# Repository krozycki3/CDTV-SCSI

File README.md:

# CDTV-SCSI

SCSI expansion board for Amiga CDTV

    - Implementation of the Commodore reference design (A575)
    - internal 50 pin SCSI connector
    - internal 68 pin SCSI connector (in 8bit mode)
    - passive termination (2x220,2x330 or 2 x 220/330 THT)
    - switchable clock 16Mhz / 7MHz for WD33C93A / AM33C93A
    - disable jumper
    - activity LED
    - supports autoconfig and autoboot (scsi.device)
    - maximum partition size with ROM v2.30: 1GB
    
The inspiration was the SCSI CDTV controller performed by Matthias Heinrichs (http://amiga.resource.cx/exp/mhcdtvscsi).

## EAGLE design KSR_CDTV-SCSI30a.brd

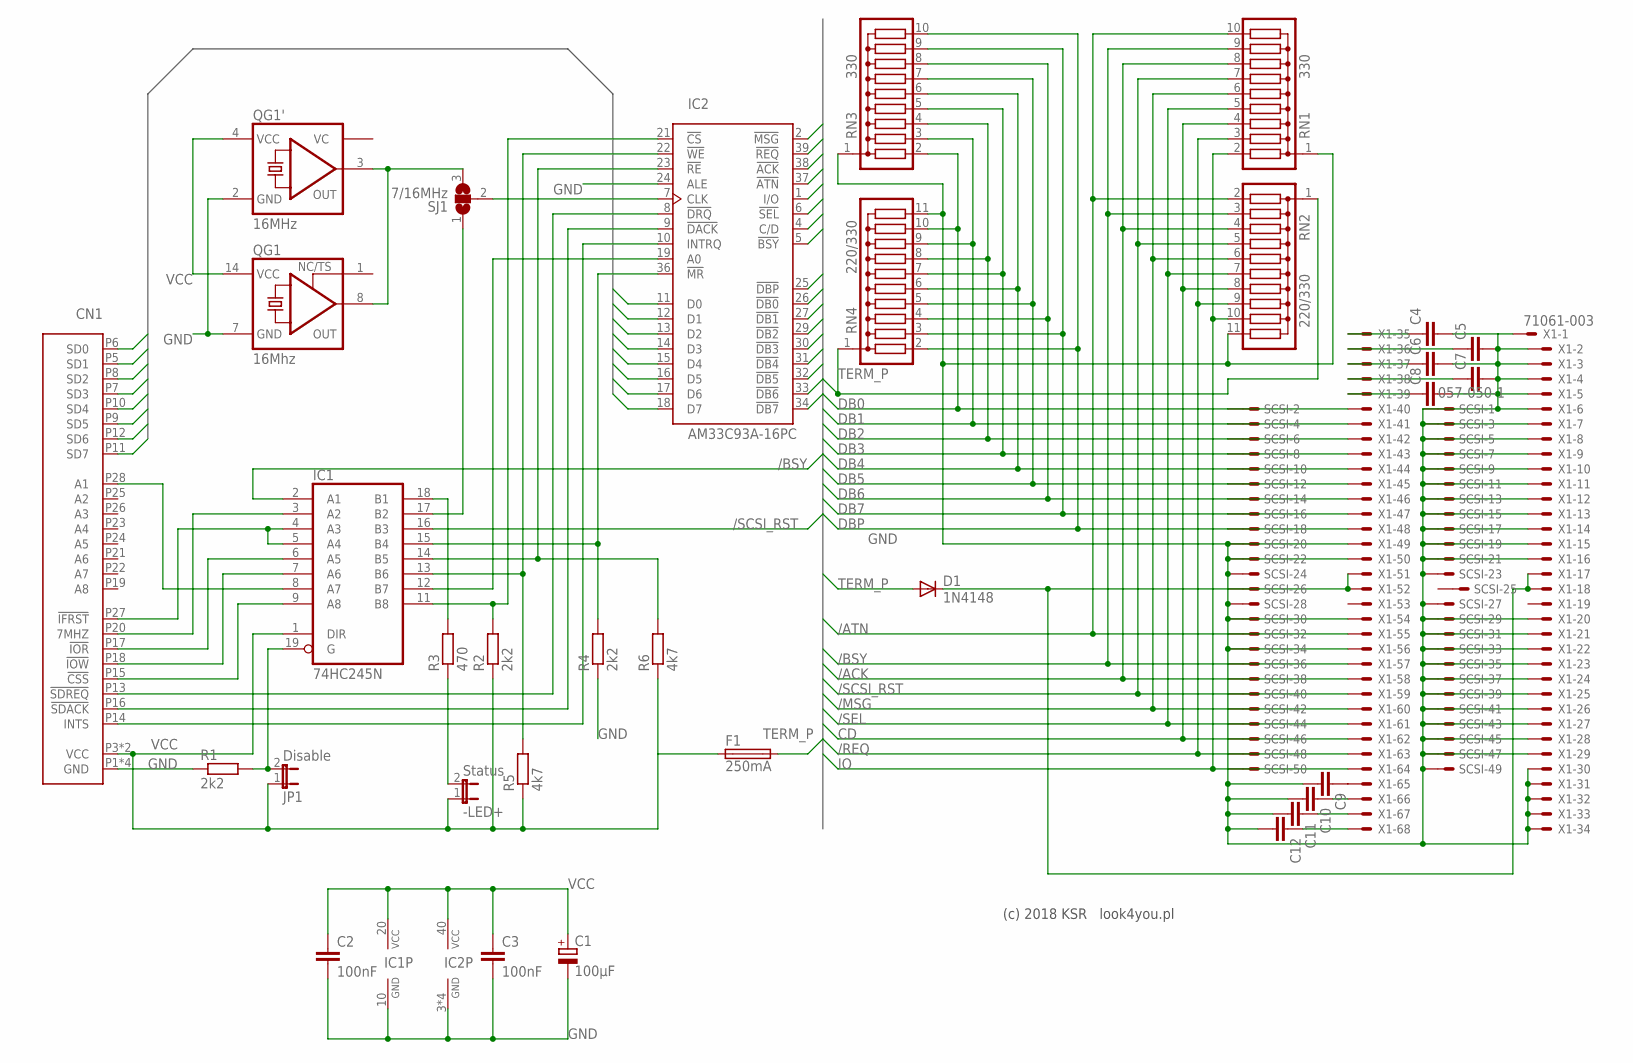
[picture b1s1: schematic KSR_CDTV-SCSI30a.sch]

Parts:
-LED+: Status; JP1
C1: 100µF; E2,5-6E
C2, C3: 100nF; C050-025X075
C4, C5, C6, C7, C8, C9, C10, C11, C12: C-EUC0603; C0603
CN1: CDTV-EXPANSION; CDTV-SLOT
D1: 1N4148; DO35-7
F1: 250mA; TE5
IC1: 74HC245N; DIL20
IC2: AM33C93A-16PC; DIP40-6
JP1: Disable; JP1
QG1: 16Mhz; DIL14S
QG1': 16MHz; 7.0X5.0-4-PAD
R1, R2, R4: 2k2; 0207/7
R3: 470; 0207/7
R5, R6: 4k7; 0207/7
RN1, RN3: 330; SIL10
RN2, RN4: 220/330; SIL11
SCSI: 057-050-1
SJ1: 7/16MHz; SJ_2
X1: 71061-003; 71061-0003

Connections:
7MHZ: CN1.P20 (7MHZ), IC1.3 (A2)
/ACK: IC2.38 (!ACK), RN1.8, RN2.4, SCSI.38, X1.58
/ATN: IC2.37 (!ATN), RN1.10, RN2.2, SCSI.32, X1.55
/BSY: IC1.2 (A1), IC2.5 (!BSY), RN1.9, RN2.3, SCSI.36, X1.57
/BSY_B: -LED+.2, R3.1
/CS: IC1.11 (B8), IC2.21 (!CS), R2.2
/CSS: CN1.P15 (!CSS), IC1.9 (A8)
/ENABLE: IC1.19 (G), JP1.2, R1.2
/IFRST: CN1.P27 (!IFRST), IC1.4 (A3), IC1.5 (A4)
/INTS: CN1.P14 (INTS), IC2.10 (INTRQ)
/IOR: CN1.P17 (!IOR), IC1.6 (A5)
/IOW: CN1.P18 (!IOW), IC1.7 (A6)
/MR: IC1.15 (B4), IC2.36 (!MR), R4.2
/MSG: IC2.2 (!MSG), RN1.6, RN2.6, SCSI.42, X1.60
/RE: IC1.14 (B5), IC2.23 (!RE), R6.2
/REQ: IC2.39 (!REQ), RN1.3, RN2.9, SCSI.48, X1.63
/SCSI_RST: IC1.16 (B3), RN1.7, RN2.5, SCSI.40, X1.59
/SDACK: CN1.P16 (!SDACK), IC2.9 (!DACK)
/SDREQ: CN1.P13 (!SDREQ), IC2.8 (!DRQ)
/SEL: IC2.6 (!SEL), RN1.5, RN2.7, SCSI.44, X1.61
/WE: IC1.13 (B6), IC2.22 (!WE), R5.2
A1: CN1.P28 (A1), IC1.8 (A7)
B_A1: IC1.12 (B7), IC2.19 (A0)
CD: IC2.4 (C/D), RN1.4, RN2.8, SCSI.46, X1.62
CLK: IC2.7 (CLK), SJ1.2
CLK_7: IC1.17 (B2), SJ1.1
CLK_16M: QG1.8 (OUT), QG1'.3 (OUT), SJ1.3
DB0: IC2.26 (!DB0), RN3.2, RN4.10, SCSI.2, X1.40
DB1: IC2.27 (!DB1), RN3.3, RN4.9, SCSI.4, X1.41
DB2: IC2.29 (!DB2), RN3.4, RN4.8, SCSI.6, X1.42
DB3: IC2.30 (!DB3), RN3.5, RN4.7, SCSI.8, X1.43
DB4: IC2.31 (!DB4), RN3.6, RN4.6, SCSI.10, X1.44
DB5: IC2.32 (!DB5), RN3.7, RN4.5, SCSI.12, X1.45
DB6: IC2.33 (!DB6), RN3.8, RN4.4, SCSI.14, X1.46
DB7: IC2.34 (!DB7), RN3.9, RN4.3, SCSI.16, X1.47
DBP: IC2.25 (!DBP), RN3.10, RN4.2, SCSI.18, X1.48
GND: C1.-, C2.2, C3.2, C4.2, C5.2, C6.2, C7.2, C8.2, C9.2, C10.2, C11.2, C12.2, CN1.P1 (GND), CN1.P2 (GND), CN1.P29 (GND), CN1.P30 (GND), IC1.10 (GND), IC2.3 (GND1), IC2.20 (GND1), IC2.24 (ALE), IC2.28 (GND1), IC2.35 (GND1), QG1.7 (GND), QG1'.2 (GND), R1.1, R4.1, RN1.1, RN2.11, RN3.1, RN4.11, SCSI.1, SCSI.3, SCSI.5, SCSI.7, SCSI.9, SCSI.11, SCSI.13, SCSI.15, SCSI.17, SCSI.19, SCSI.20, SCSI.21, SCSI.22, SCSI.23, SCSI.24, SCSI.27, SCSI.28, SCSI.29, SCSI.30, SCSI.31, SCSI.33, SCSI.34, SCSI.35, SCSI.37, SCSI.39, SCSI.41, SCSI.43, SCSI.45, SCSI.47, SCSI.49, X1.1, X1.2, X1.3, X1.4, X1.5, X1.6, X1.7, X1.8, X1.9, X1.10, X1.11, X1.12, X1.13, X1.14, X1.15, X1.16, X1.20, X1.21, X1.22, X1.23, X1.24, X1.25, X1.26, X1.27, X1.28, X1.29, X1.30, X1.31, X1.32, X1.33, X1.34, X1.49, X1.50, X1.54, X1.56
IO: IC2.1 (I/O), RN1.2, RN2.10, SCSI.50, X1.64
unnamed: IC1.18 (B1), R3.2
unnamed: D1.C, SCSI.26, X1.17, X1.18, X1.51, X1.52
unnamed: C9.1, X1.65
unnamed: C10.1, X1.66
unnamed: C11.1, X1.67
unnamed: C12.1, X1.68
unnamed: C8.1, X1.39
unnamed: C7.1, X1.38
unnamed: C6.1, X1.37
unnamed: C5.1, X1.36
unnamed: C4.1, X1.35
SD0: CN1.P6 (SD0), IC2.11 (D0)
SD1: CN1.P5 (SD1), IC2.12 (D1)
SD2: CN1.P8 (SD2), IC2.13 (D2)
SD3: CN1.P7 (SD3), IC2.14 (D3)
SD4: CN1.P10 (SD4), IC2.15 (D4)
SD5: CN1.P9 (SD5), IC2.16 (D5)
SD6: CN1.P12 (SD6), IC2.17 (D6)
SD7: CN1.P11 (SD7), IC2.18 (D7)
TERM_P: D1.A, F1.2, RN2.1, RN4.1
VCC: -LED+.1, C1.+, C2.1, C3.1, CN1.P3 (VCC), CN1.P4 (VCC), F1.1, IC1.1 (DIR), IC1.20 (VCC), IC2.40 (VCC1), JP1.1, QG1.14 (VCC), QG1'.4 (VCC), R2.1, R5.1, R6.1

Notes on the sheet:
(c) 2018 KSR look4you.pl

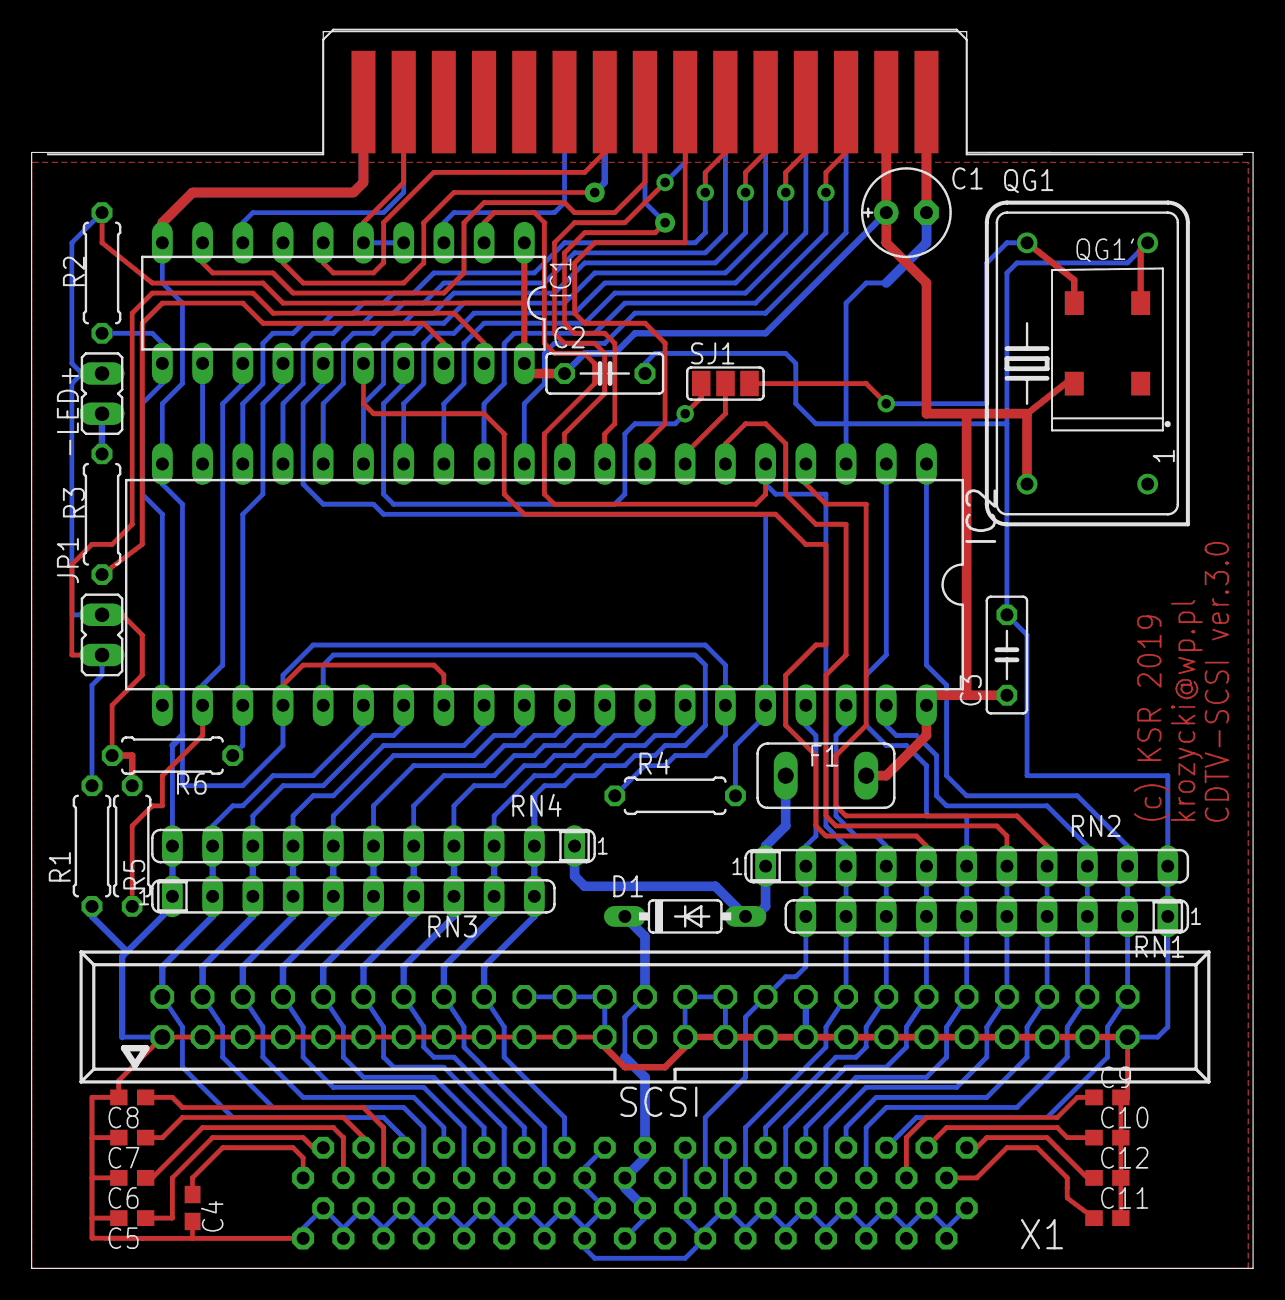
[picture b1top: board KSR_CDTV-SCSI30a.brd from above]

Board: 2 copper layers, 77.1 x 78.1 mm, 34 parts (0 on the bottom side), 59 nets.
